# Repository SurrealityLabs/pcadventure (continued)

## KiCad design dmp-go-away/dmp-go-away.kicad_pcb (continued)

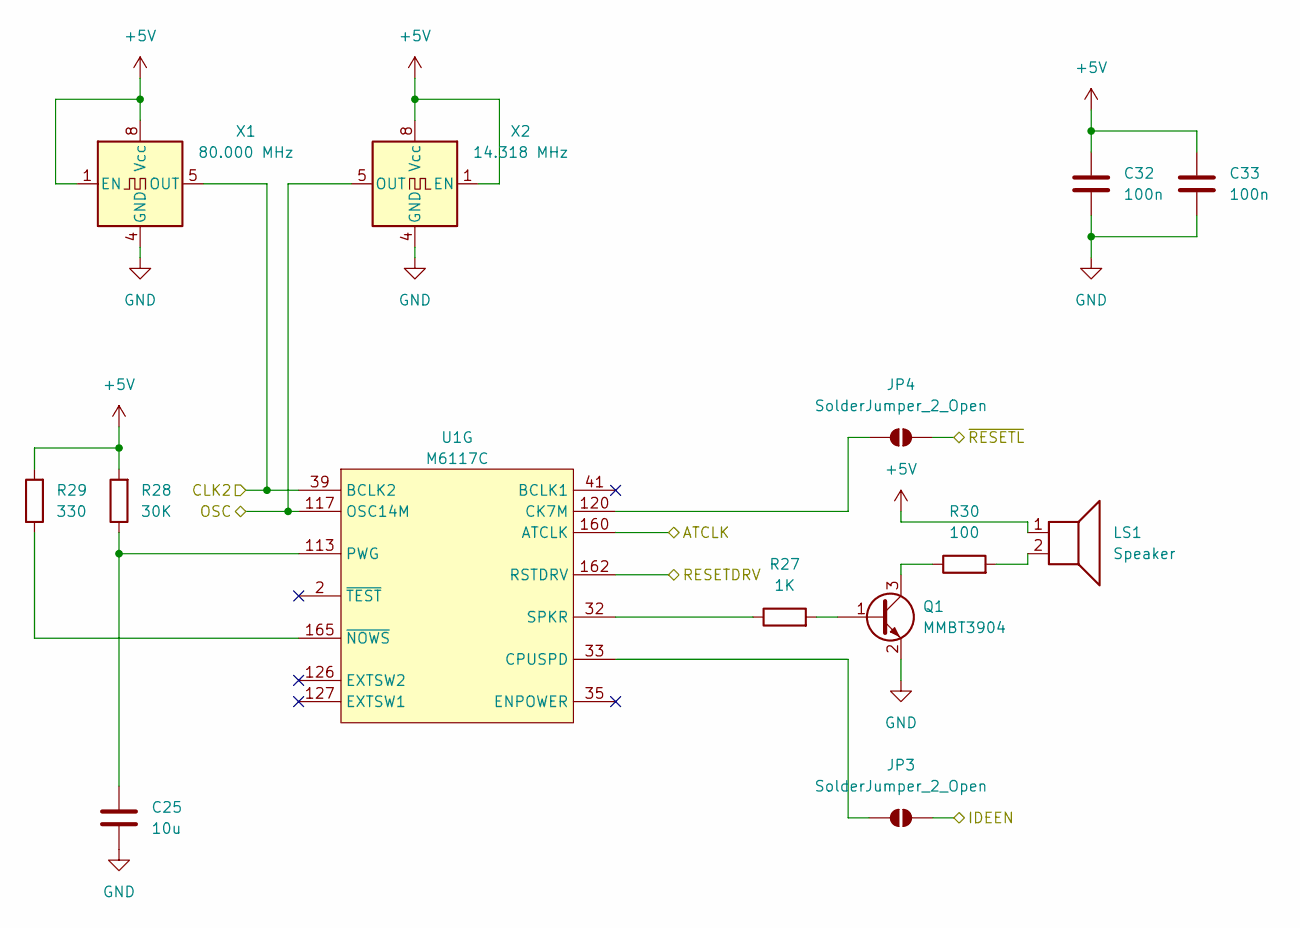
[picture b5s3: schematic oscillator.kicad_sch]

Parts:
C25: 10u; C_1206_3216Metric_Pad1.33x1.80mm_HandSolder
C32, C33: 100n; C_0603_1608Metric_Pad1.08x0.95mm_HandSolder
JP3, JP4: SolderJumper_2_Open; SolderJumper-2_P1.3mm_Open_RoundedPad1.0x1.5mm
LS1: Speaker; Buzzer_TDK_PS1240P02BT_D12.2mm_H6.5mm
Q1: MMBT3904; SOT-23
R27: 1K; R_0603_1608Metric_Pad0.98x0.95mm_HandSolder
R28: 30K; R_0603_1608Metric_Pad0.98x0.95mm_HandSolder
R29: 330; R_0603_1608Metric_Pad0.98x0.95mm_HandSolder
R30: 100; R_0603_1608Metric_Pad0.98x0.95mm_HandSolder
U1: M6117C; PQFP-208_28x28mm_P0.5mm
X1: 80.000 MHz; Oscillator_DIP-8; Digikey XC283-ND
X2: 14.318 MHz; Oscillator_DIP-8; Digikey 110-MXO45HS-3C-14M318180-ND

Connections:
+5V: C32.1, C33.1, LS1.1, R28.2, R29.2, X1.1 (EN), X1.8 (Vcc), X2.1 (EN), X2.8 (Vcc); also elsewhere on the board
/ATCLK: U1.160 (ATCLK); also elsewhere on the board
/IDEEN: JP3.2 (B); also elsewhere on the board
/OSC: U1.117 (OSC14M), X2.5 (OUT); also elsewhere on the board
/Oscillator/CLK2: U1.39 (BCLK2), X1.5 (OUT)
/RESETDRV: U1.162 (RSTDRV); also elsewhere on the board
/~RESETL: JP4.2 (B); also elsewhere on the board
GND: C25.2, C32.2, C33.2, Q1.2 (E), X1.4 (GND), X2.4 (GND); also elsewhere on the board
unnamed: JP3.1 (A), U1.33 (CPUSPD)
unnamed: JP4.1 (A), U1.120 (CK7M)
unnamed: LS1.2, R30.2
unnamed: Q1.1 (B), R27.2
unnamed: Q1.3 (C), R30.1
unnamed: C25.1, R28.1, U1.113 (PWG)
unnamed: R27.1, U1.32 (SPKR)
unnamed: R29.1, U1.165 (~NOWS)

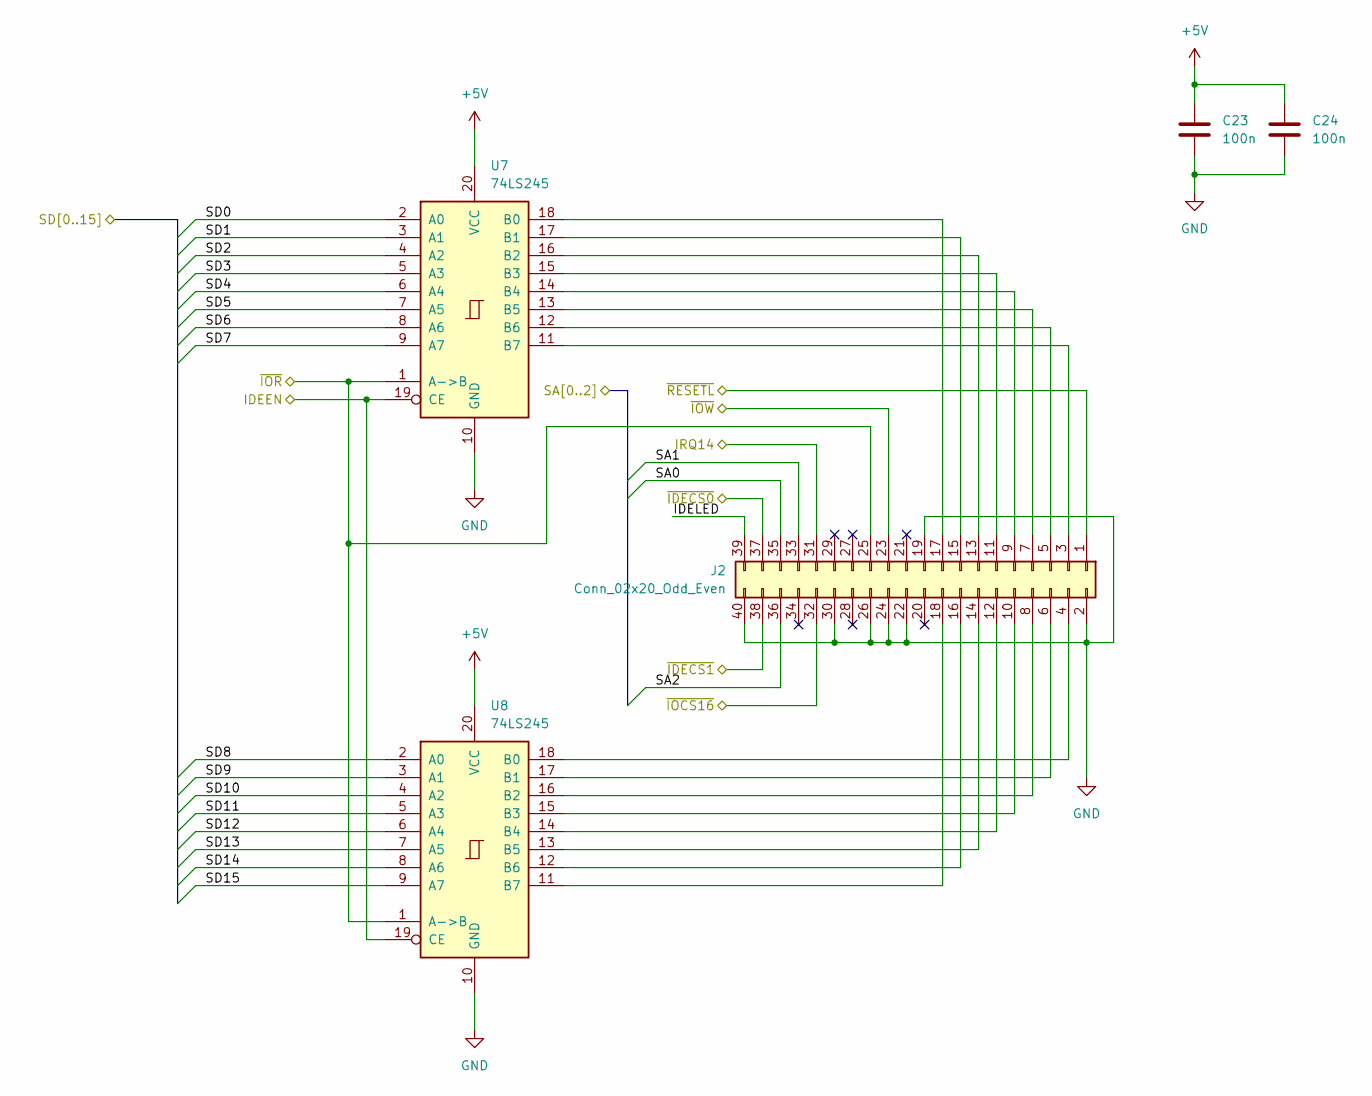
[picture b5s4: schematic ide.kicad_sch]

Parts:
C23, C24: 100n; C_0603_1608Metric_Pad1.08x0.95mm_HandSolder
J2: Conn_02x20_Odd_Even; IDC-Header_2x20_P2.54mm_Vertical
U7, U8: 74LS245; SOIC-20W_7.5x12.8mm_P1.27mm

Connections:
+5V: C23.1, C24.1, U7.20 (VCC), U8.20 (VCC); also elsewhere on the board
/IDE/IDELED: J2.39
/IDEEN: U7.19 (CE), U8.19 (CE); also elsewhere on the board
/IRQ14: J2.31; also elsewhere on the board
/SA0: J2.35; also elsewhere on the board
/SA1: J2.33; also elsewhere on the board
/SA2: J2.36; also elsewhere on the board
/SD0: U7.2 (A0); also elsewhere on the board
/SD1: U7.3 (A1); also elsewhere on the board
/SD2: U7.4 (A2); also elsewhere on the board
/SD3: U7.5 (A3); also elsewhere on the board
/SD4: U7.6 (A4); also elsewhere on the board
/SD5: U7.7 (A5); also elsewhere on the board
/SD6: U7.8 (A6); also elsewhere on the board
/SD7: U7.9 (A7); also elsewhere on the board
/SD8: U8.2 (A0); also elsewhere on the board
/SD9: U8.3 (A1); also elsewhere on the board
/SD10: U8.4 (A2); also elsewhere on the board
/SD11: U8.5 (A3); also elsewhere on the board
/SD12: U8.6 (A4); also elsewhere on the board
/SD13: U8.7 (A5); also elsewhere on the board
/SD14: U8.8 (A6); also elsewhere on the board
/SD15: U8.9 (A7); also elsewhere on the board
/~IDECS0: J2.37; also elsewhere on the board
/~IDECS1: J2.38; also elsewhere on the board
/~IO16: J2.32; also elsewhere on the board
/~IOR: J2.25, U7.1 (A->B), U8.1 (A->B); also elsewhere on the board
/~IOW: J2.23; also elsewhere on the board
/~RESETL: J2.1; also elsewhere on the board
GND: C23.2, C24.2, J2.2, J2.19, J2.22, J2.24, J2.26, J2.30, J2.40, U7.10 (GND), U8.10 (GND); also elsewhere on the board
unnamed: J2.3, U7.11 (B7)
unnamed: J2.4, U8.18 (B0)
unnamed: J2.5, U7.12 (B6)
unnamed: J2.6, U8.17 (B1)
unnamed: J2.7, U7.13 (B5)
unnamed: J2.8, U8.16 (B2)
unnamed: J2.9, U7.14 (B4)
unnamed: J2.10, U8.15 (B3)
unnamed: J2.11, U7.15 (B3)
unnamed: J2.12, U8.14 (B4)
unnamed: J2.13, U7.16 (B2)
unnamed: J2.14, U8.13 (B5)
unnamed: J2.15, U7.17 (B1)
unnamed: J2.16, U8.12 (B6)
unnamed: J2.17, U7.18 (B0)
unnamed: J2.18, U8.11 (B7)

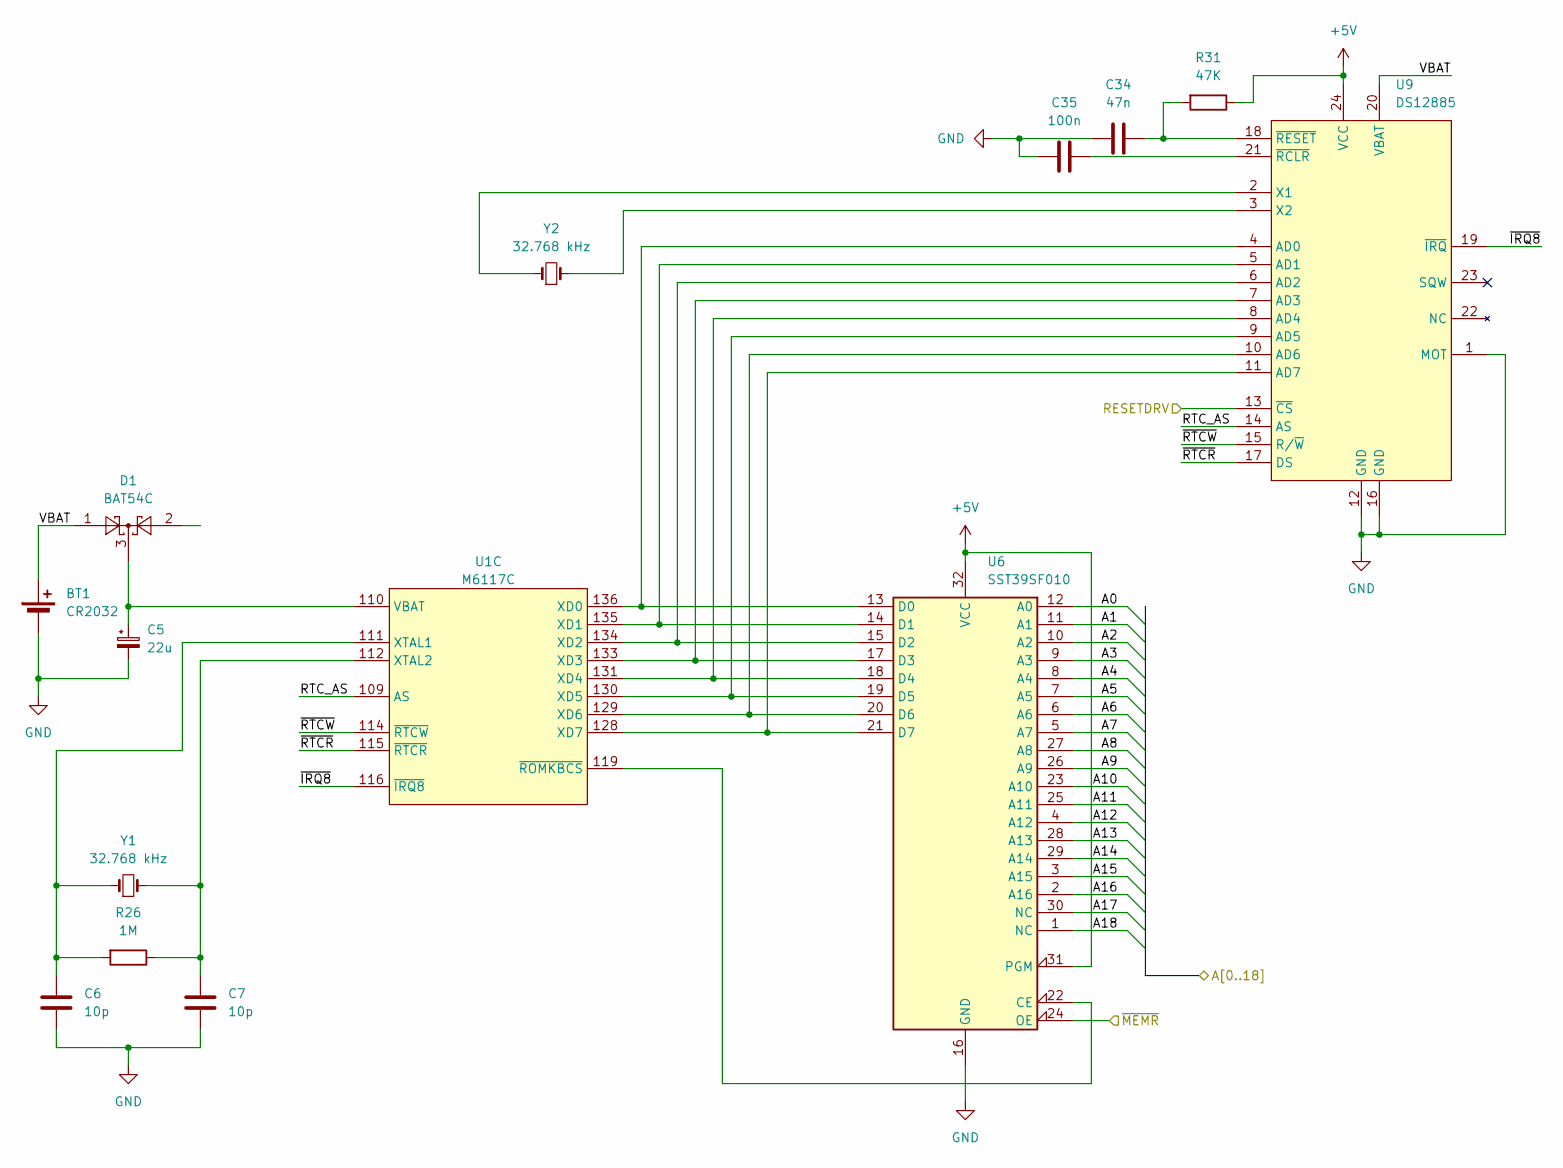
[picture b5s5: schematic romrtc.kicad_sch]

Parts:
BT1: CR2032; BatteryHolder_Keystone_1060_1x2032
C5: 22u; CP_Elec_5x5.3
C6, C7: 10p; C_0603_1608Metric_Pad1.08x0.95mm_HandSolder
C34: 47n; C_0603_1608Metric_Pad1.08x0.95mm_HandSolder
C35: 100n; C_0603_1608Metric_Pad1.08x0.95mm_HandSolder
D1: BAT54C; SOT-23
R26: 1M; R_0603_1608Metric_Pad0.98x0.95mm_HandSolder
R31: 47K; R_0603_1608Metric_Pad0.98x0.95mm_HandSolder
U1: M6117C; PQFP-208_28x28mm_P0.5mm
U6: SST39SF010; DIP-32_W15.24mm_Socket
U9: DS12885; DIP-24_W15.24mm
Y1, Y2: 32.768 kHz; Crystal_AT310_D3.0mm_L10.0mm_Vertical

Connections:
+5V: R31.1, U6.31 (PGM), U6.32 (VCC), U9.24 (VCC); also elsewhere on the board
/RESETDRV: U9.13 (~CS); also elsewhere on the board
/ROM RTC/RTC_AS: U1.109 (AS), U9.14 (AS)
/ROM RTC/VBAT: BT1.1 (+), D1.1, U9.20 (VBAT)
/ROM RTC/~IRQ8: U1.116 (~IRQ8), U9.19 (~IRQ)
/ROM RTC/~RTCR: U1.115 (~RTCR), U9.17 (DS)
/ROM RTC/~RTCW: U1.114 (~RTCW), U9.15 (R/~W)
/SA0: U6.12 (A0); also elsewhere on the board
/SA1: U6.11 (A1); also elsewhere on the board
/SA2: U6.10 (A2); also elsewhere on the board
/SA3: U6.9 (A3); also elsewhere on the board
/SA4: U6.8 (A4); also elsewhere on the board
/SA5: U6.7 (A5); also elsewhere on the board
/SA6: U6.6 (A6); also elsewhere on the board
/SA7: U6.5 (A7); also elsewhere on the board
/SA8: U6.27 (A8); also elsewhere on the board
/SA9: U6.26 (A9); also elsewhere on the board
/SA10: U6.23 (A10); also elsewhere on the board
/SA11: U6.25 (A11); also elsewhere on the board
/SA12: U6.4 (A12); also elsewhere on the board
/SA13: U6.28 (A13); also elsewhere on the board
/SA14: U6.29 (A14); also elsewhere on the board
/SA15: U6.3 (A15); also elsewhere on the board
/SA16: U6.2 (A16); also elsewhere on the board
/SA17: U6.30 (NC); also elsewhere on the board
/SA18: U6.1 (NC); also elsewhere on the board
/~MEMR: U6.24 (OE)
GND: BT1.2 (-), C5.2, C6.2, C7.2, C34.2, C35.2, U6.16 (GND), U9.1 (MOT), U9.12 (GND), U9.16 (GND); also elsewhere on the board
unnamed: C5.1, D1.3, U1.110 (VBAT)
unnamed: U1.136 (XD0), U6.13 (D0), U9.4 (AD0)
unnamed: U1.135 (XD1), U6.14 (D1), U9.5 (AD1)
unnamed: U1.134 (XD2), U6.15 (D2), U9.6 (AD2)
unnamed: U1.133 (XD3), U6.17 (D3), U9.7 (AD3)
unnamed: U1.131 (XD4), U6.18 (D4), U9.8 (AD4)
unnamed: U1.130 (XD5), U6.19 (D5), U9.9 (AD5)
unnamed: U1.129 (XD6), U6.20 (D6), U9.10 (AD6)
unnamed: U1.128 (XD7), U6.21 (D7), U9.11 (AD7)
unnamed: C6.1, R26.2, U1.111 (XTAL1), Y1.1
unnamed: C7.1, R26.1, U1.112 (XTAL2), Y1.2
unnamed: U1.119 (~ROMKBCS), U6.22 (CE)
unnamed: U9.2 (X1), Y2.1
unnamed: U9.3 (X2), Y2.2
unnamed: C35.1, U9.21 (~RCLR)
unnamed: C34.1, R31.2, U9.18 (~RESET)

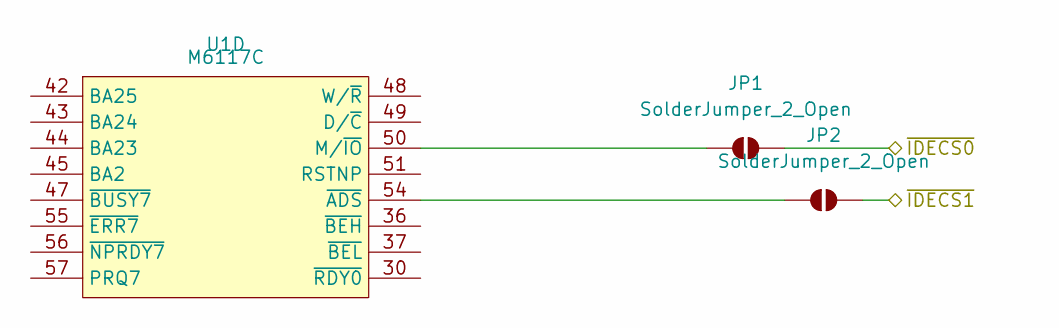
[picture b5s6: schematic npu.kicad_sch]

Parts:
JP1, JP2: SolderJumper_2_Open; SolderJumper-2_P1.3mm_Open_RoundedPad1.0x1.5mm
U1: M6117C; PQFP-208_28x28mm_P0.5mm

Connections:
/~IDECS0: JP1.2 (B); also elsewhere on the board
/~IDECS1: JP2.2 (B); also elsewhere on the board
unnamed: JP1.1 (A), U1.50 (M/~IO)
unnamed: JP2.1 (A), U1.54 (~ADS)

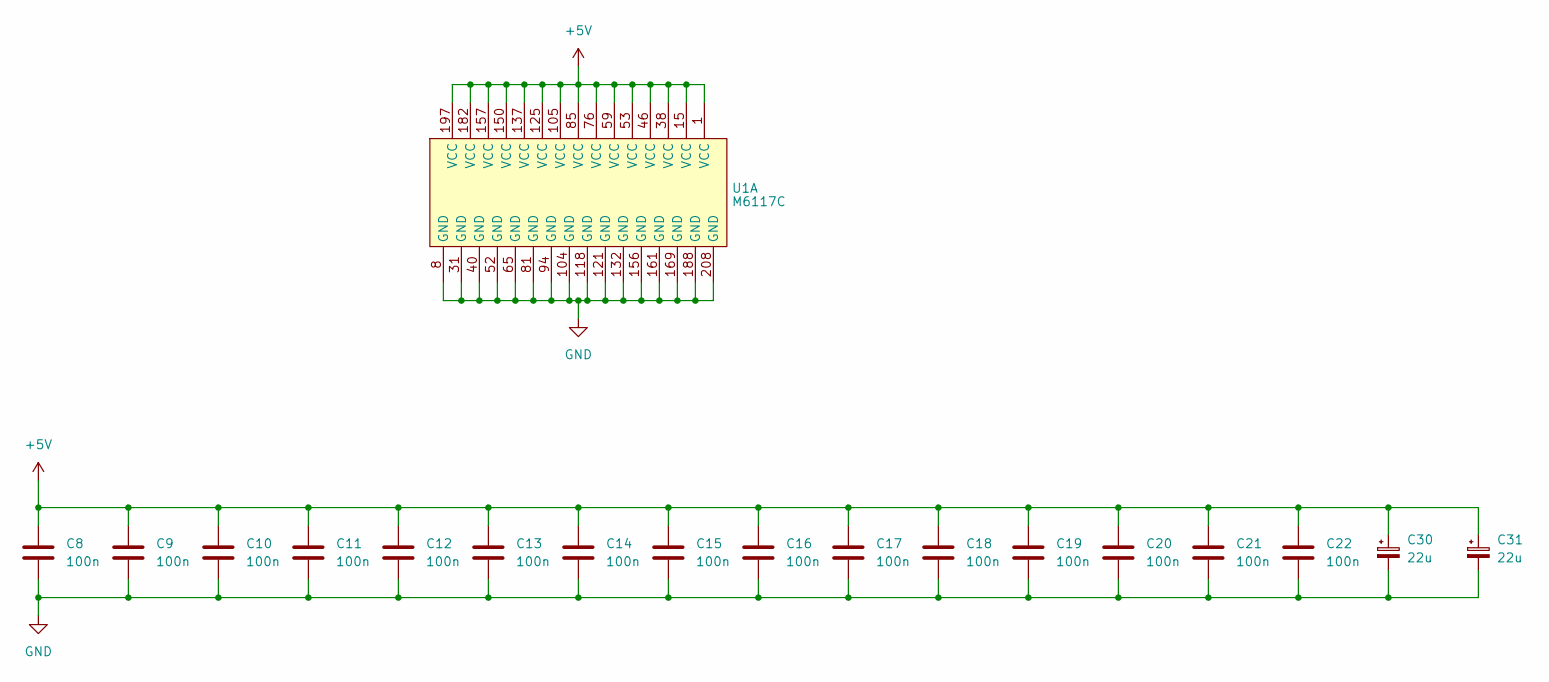
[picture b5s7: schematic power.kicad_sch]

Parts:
C8, C9, C10, C11, C12, C13, C14, C15, C16, C17, C18, C19, C20, C21, C22: 100n; C_0603_1608Metric_Pad1.08x0.95mm_HandSolder
C30, C31: 22u; CP_Elec_5x5.3
U1: M6117C; PQFP-208_28x28mm_P0.5mm

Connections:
+5V: C8.1, C9.1, C10.1, C11.1, C12.1, C13.1, C14.1, C15.1, C16.1, C17.1, C18.1, C19.1, C20.1, C21.1, C22.1, C30.1, C31.1, U1.1 (VCC), U1.15 (VCC), U1.38 (VCC), U1.46 (VCC), U1.53 (VCC), U1.59 (VCC), U1.76 (VCC), U1.85 (VCC), U1.105 (VCC), U1.125 (VCC), U1.137 (VCC), U1.150 (VCC), U1.157 (VCC), U1.182 (VCC), U1.197 (VCC); also elsewhere on the board
GND: C8.2, C9.2, C10.2, C11.2, C12.2, C13.2, C14.2, C15.2, C16.2, C17.2, C18.2, C19.2, C20.2, C21.2, C22.2, C30.2, C31.2, U1.8 (GND), U1.31 (GND), U1.40 (GND), U1.52 (GND), U1.65 (GND), U1.81 (GND), U1.94 (GND), U1.104 (GND), U1.118 (GND), U1.121 (GND), U1.132 (GND), U1.156 (GND), U1.161 (GND), U1.169 (GND), U1.188 (GND), U1.208 (GND); also elsewhere on the board

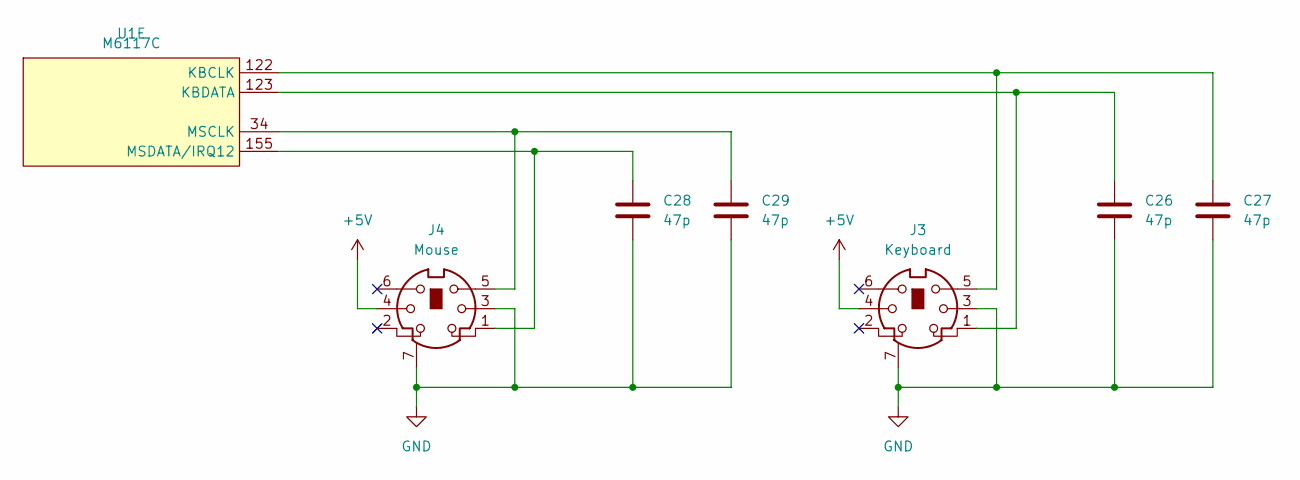
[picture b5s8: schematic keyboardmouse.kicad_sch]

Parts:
C26, C27, C28, C29: 47p; C_0603_1608Metric_Pad1.08x0.95mm_HandSolder
J3: Keyboard; CUI_MD-60SGK
J4: Mouse; CUI_MD-60SGK
U1: M6117C; PQFP-208_28x28mm_P0.5mm

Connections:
+5V: J3.4, J4.4; also elsewhere on the board
GND: C26.2, C27.2, C28.2, C29.2, J3.3, J3.7, J4.3, J4.7; also elsewhere on the board
unnamed: C27.1, J3.5, U1.122 (KBCLK)
unnamed: C26.1, J3.1, U1.123 (KBDATA)
unnamed: C29.1, J4.5, U1.34 (MSCLK)
unnamed: C28.1, J4.1, U1.155 (MSDATA/IRQ12)

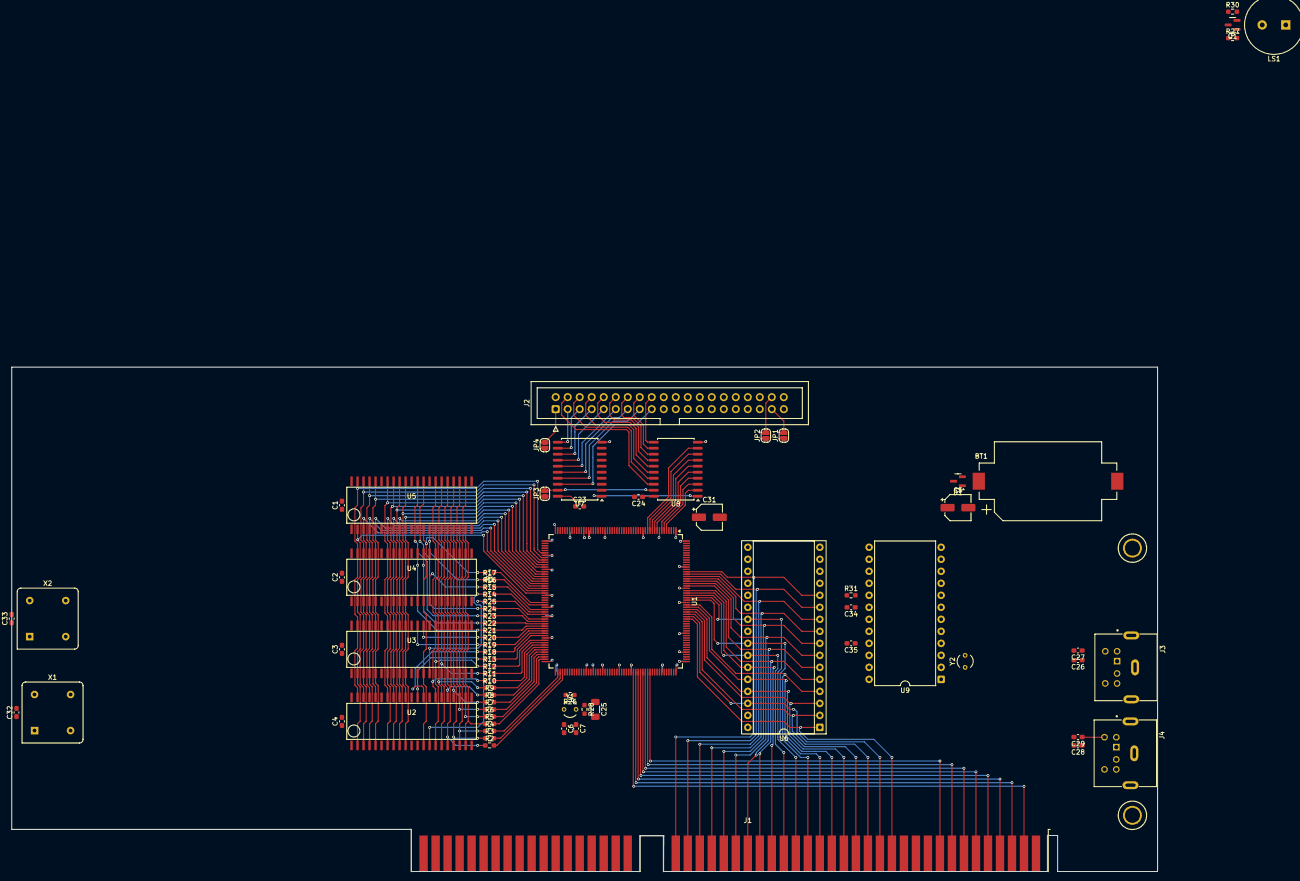
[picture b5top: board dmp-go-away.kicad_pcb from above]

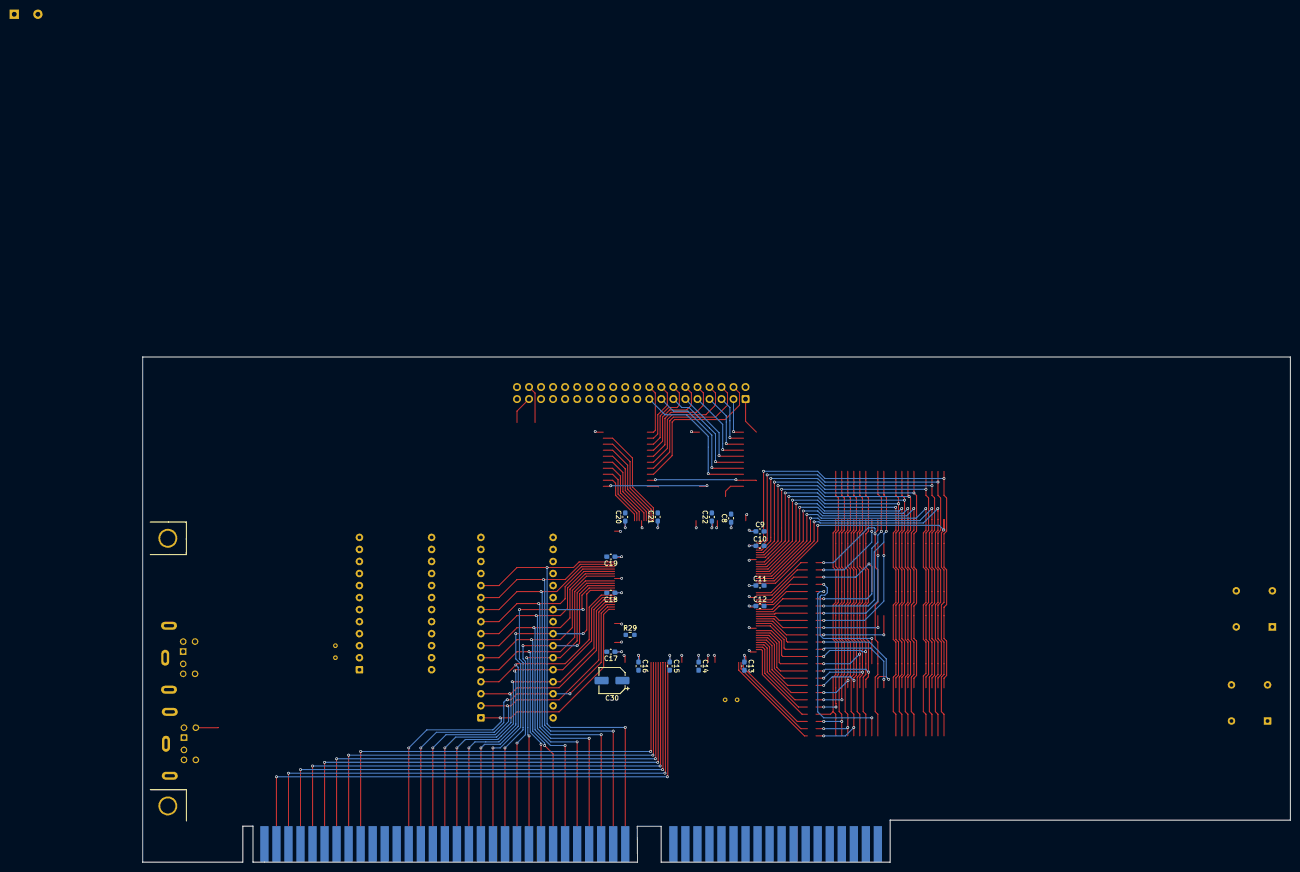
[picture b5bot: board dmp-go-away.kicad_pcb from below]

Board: 2 copper layers, 242.4 x 106.7 mm, 92 parts (17 on the bottom side), 210 nets.

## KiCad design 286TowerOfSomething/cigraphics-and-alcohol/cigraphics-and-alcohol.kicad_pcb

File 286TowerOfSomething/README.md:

THE PLAN:
- I have a 14-slot ISA backplane from Surplus Gizmos. That will form the basis of the system. Because there are so many slots on the backplane, the individual cards can be single-function (allowing a smaller and therefore cheaper PCB)
- CPU, ROM, RAM, Chipset, and keyboard controller will go on an ISA card.
- Video card will be a TVGA8900D card that I already ordered.
- I will make a dual 16C550-based serial card, with an option to convert one serial port to a PS/2 mouse input through an ATMEGA328P running some open-source firmware. That covers serial port and mouse input.
- I will make a 16-bit IDE card (using a PAL and some bus transceivers) that has an Option ROM containing the XTIDE BIOS. That'll provide fixed storage (through CF card, optical drive, or SD to IDE adapter)
- I will make a parallel card using an EPP/ECP parallel port controller, so that we can add things like ZIP drives or scanners or what not if we find them.
- I will make a floppy controller using a floppy controller to be named later
- For sound card, probably a PicoGUS or whatever Cirrus Logic chip I have available
- Something simple for Ethernet, like an RTL8019. Might be cheaper to build one than buy one at this point - the chip is $5, and cards are going for like $40+. Pretty sure those were $10-$20 when new.
- For convenience, a CH375-based USB mass storage card.

FUTURE PLANS:
- Can make an upgraded CPU card with an M6117D chip from DM&P/nVidia. 386SX 40 MHz system on a chip, might still be made in 2024.
- Can make an upgraded CPU card with a 486 chip and chipset, if we can find one. Add VLB video onto that card for faaaaaast gaming - has to be on the card, though, because the backplane won't do VLB.

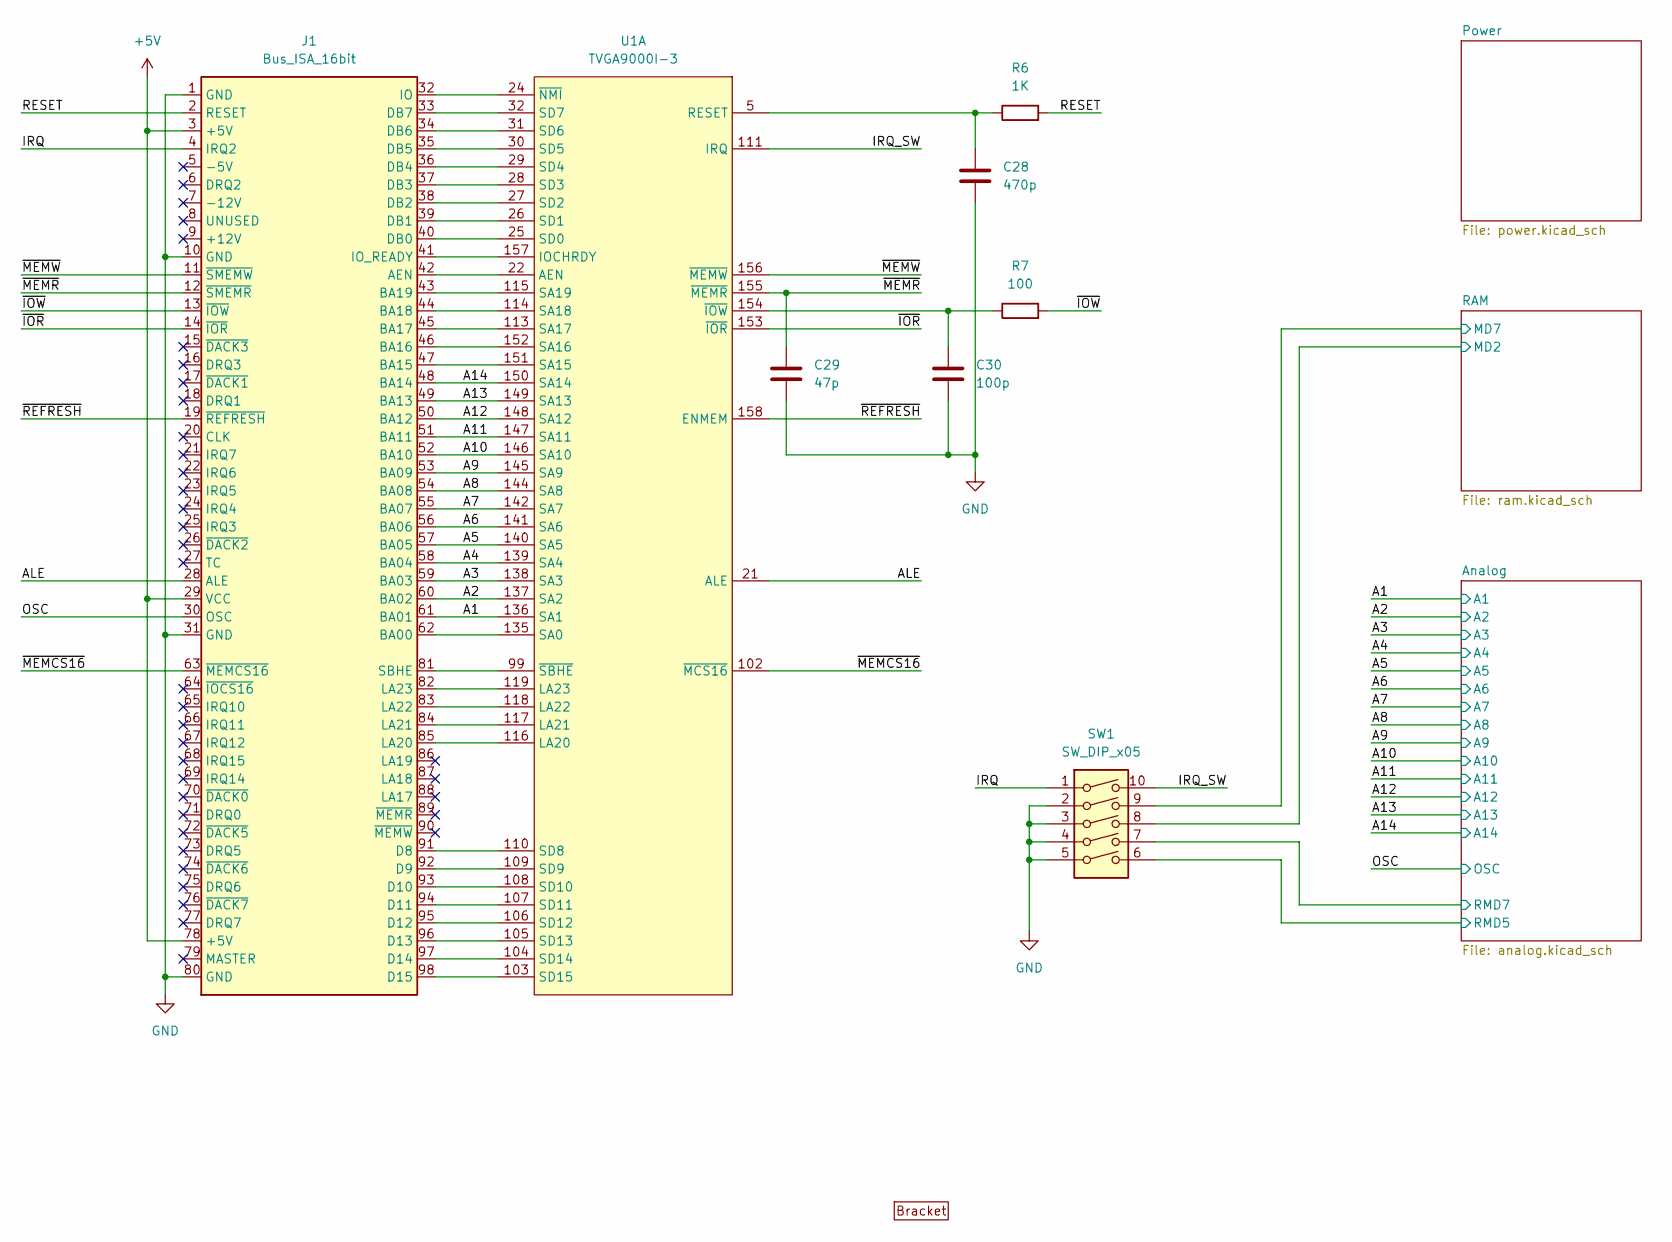
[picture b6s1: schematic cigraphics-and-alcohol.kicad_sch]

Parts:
C28: 470p; C_0603_1608Metric_Pad1.08x0.95mm_HandSolder
C29: 47p; C_0603_1608Metric_Pad1.08x0.95mm_HandSolder
C30: 100p; C_0603_1608Metric_Pad1.08x0.95mm_HandSolder
J1: Bus_ISA_16bit; BUS_AT
R6: 1K; R_0603_1608Metric_Pad0.98x0.95mm_HandSolder
R7: 100; R_0603_1608Metric_Pad0.98x0.95mm_HandSolder
SW1: SW_DIP_x05; SW_DIP_SPSTx05_Slide_9.78x14.88mm_W7.62mm_P2.54mm
U1: TVGA9000I-3; PQFP-160_28x28mm_P0.65mm
U7: PC_BRACKET_ISA_KEYSTONE_9200_Rev1_1

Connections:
+5V: J1.3 (+5V), J1.29 (VCC), J1.78 (+5V); also elsewhere on the board
/A1: J1.61 (BA01), U1.136 (SA1); also elsewhere on the board
/A2: J1.60 (BA02), U1.137 (SA2); also elsewhere on the board
/A3: J1.59 (BA03), U1.138 (SA3); also elsewhere on the board
/A4: J1.58 (BA04), U1.139 (SA4); also elsewhere on the board
/A5: J1.57 (BA05), U1.140 (SA5); also elsewhere on the board
/A6: J1.56 (BA06), U1.141 (SA6); also elsewhere on the board
/A7: J1.55 (BA07), U1.142 (SA7); also elsewhere on the board
/A8: J1.54 (BA08), U1.144 (SA8); also elsewhere on the board
/A9: J1.53 (BA09), U1.145 (SA9); also elsewhere on the board
/A10: J1.52 (BA10), U1.146 (SA10); also elsewhere on the board
/A11: J1.51 (BA11), U1.147 (SA11); also elsewhere on the board
/A12: J1.50 (BA12), U1.148 (SA12); also elsewhere on the board
/A13: J1.49 (BA13), U1.149 (SA13); also elsewhere on the board
/A14: J1.48 (BA14), U1.150 (SA14); also elsewhere on the board
/ALE: J1.28 (ALE), U1.21 (ALE)
/Analog/RMD5: SW1.6; also elsewhere on the board
/Analog/RMD7: SW1.7; also elsewhere on the board
/IRQ: J1.4 (IRQ2), SW1.1
/IRQ_SW: SW1.10, U1.111 (IRQ)
/OSC: J1.30 (OSC); also elsewhere on the board
/RAM/MD2: SW1.8; also elsewhere on the board
/RAM/MD7: SW1.9; also elsewhere on the board
/RESET: J1.2 (RESET), R6.2
/~IOR: J1.14 (~IOR), U1.153 (~IOR)
/~IOW: J1.13 (~IOW), R7.2
/~MEMCS16: J1.63 (~MEMCS16), U1.102 (~MCS16)
/~MEMR: C29.1, J1.12 (~SMEMR), U1.155 (~MEMR)
/~MEMW: J1.11 (~SMEMW), U1.156 (~MEMW)
/~REFRESH: J1.19 (~REFRESH), U1.158 (ENMEM)
GND: C28.2, C29.2, C30.2, J1.1 (GND), J1.10 (GND), J1.31 (GND), J1.80 (GND), SW1.2, SW1.3, SW1.4, SW1.5; also elsewhere on the board
unnamed: J1.42 (AEN), U1.22 (AEN)
unnamed: J1.62 (BA00), U1.135 (SA0)
unnamed: J1.47 (BA15), U1.151 (SA15)
unnamed: J1.46 (BA16), U1.152 (SA16)
unnamed: J1.45 (BA17), U1.113 (SA17)
unnamed: J1.44 (BA18), U1.114 (SA18)
unnamed: J1.43 (BA19), U1.115 (SA19)
unnamed: J1.91 (D8), U1.110 (SD8)
unnamed: J1.92 (D9), U1.109 (SD9)
unnamed: J1.93 (D10), U1.108 (SD10)
unnamed: J1.94 (D11), U1.107 (SD11)
unnamed: J1.95 (D12), U1.106 (SD12)
unnamed: J1.96 (D13), U1.105 (SD13)
unnamed: J1.97 (D14), U1.104 (SD14)
unnamed: J1.98 (D15), U1.103 (SD15)
unnamed: J1.40 (DB0), U1.25 (SD0)
unnamed: J1.39 (DB1), U1.26 (SD1)
unnamed: J1.38 (DB2), U1.27 (SD2)
unnamed: J1.37 (DB3), U1.28 (SD3)
unnamed: J1.36 (DB4), U1.29 (SD4)
unnamed: J1.35 (DB5), U1.30 (SD5)
unnamed: J1.34 (DB6), U1.31 (SD6)
unnamed: J1.33 (DB7), U1.32 (SD7)
unnamed: J1.32 (IO), U1.24 (~NMI)
unnamed: J1.41 (IO_READY), U1.157 (IOCHRDY)
unnamed: J1.85 (LA20), U1.116 (LA20)
unnamed: J1.84 (LA21), U1.117 (LA21)
unnamed: J1.83 (LA22), U1.118 (LA22)
unnamed: J1.82 (LA23), U1.119 (LA23)
unnamed: J1.81 (SBHE), U1.99 (~SBHE)
unnamed: C28.1, R6.1, U1.5 (RESET)
unnamed: C30.1, R7.1, U1.154 (~IOW)

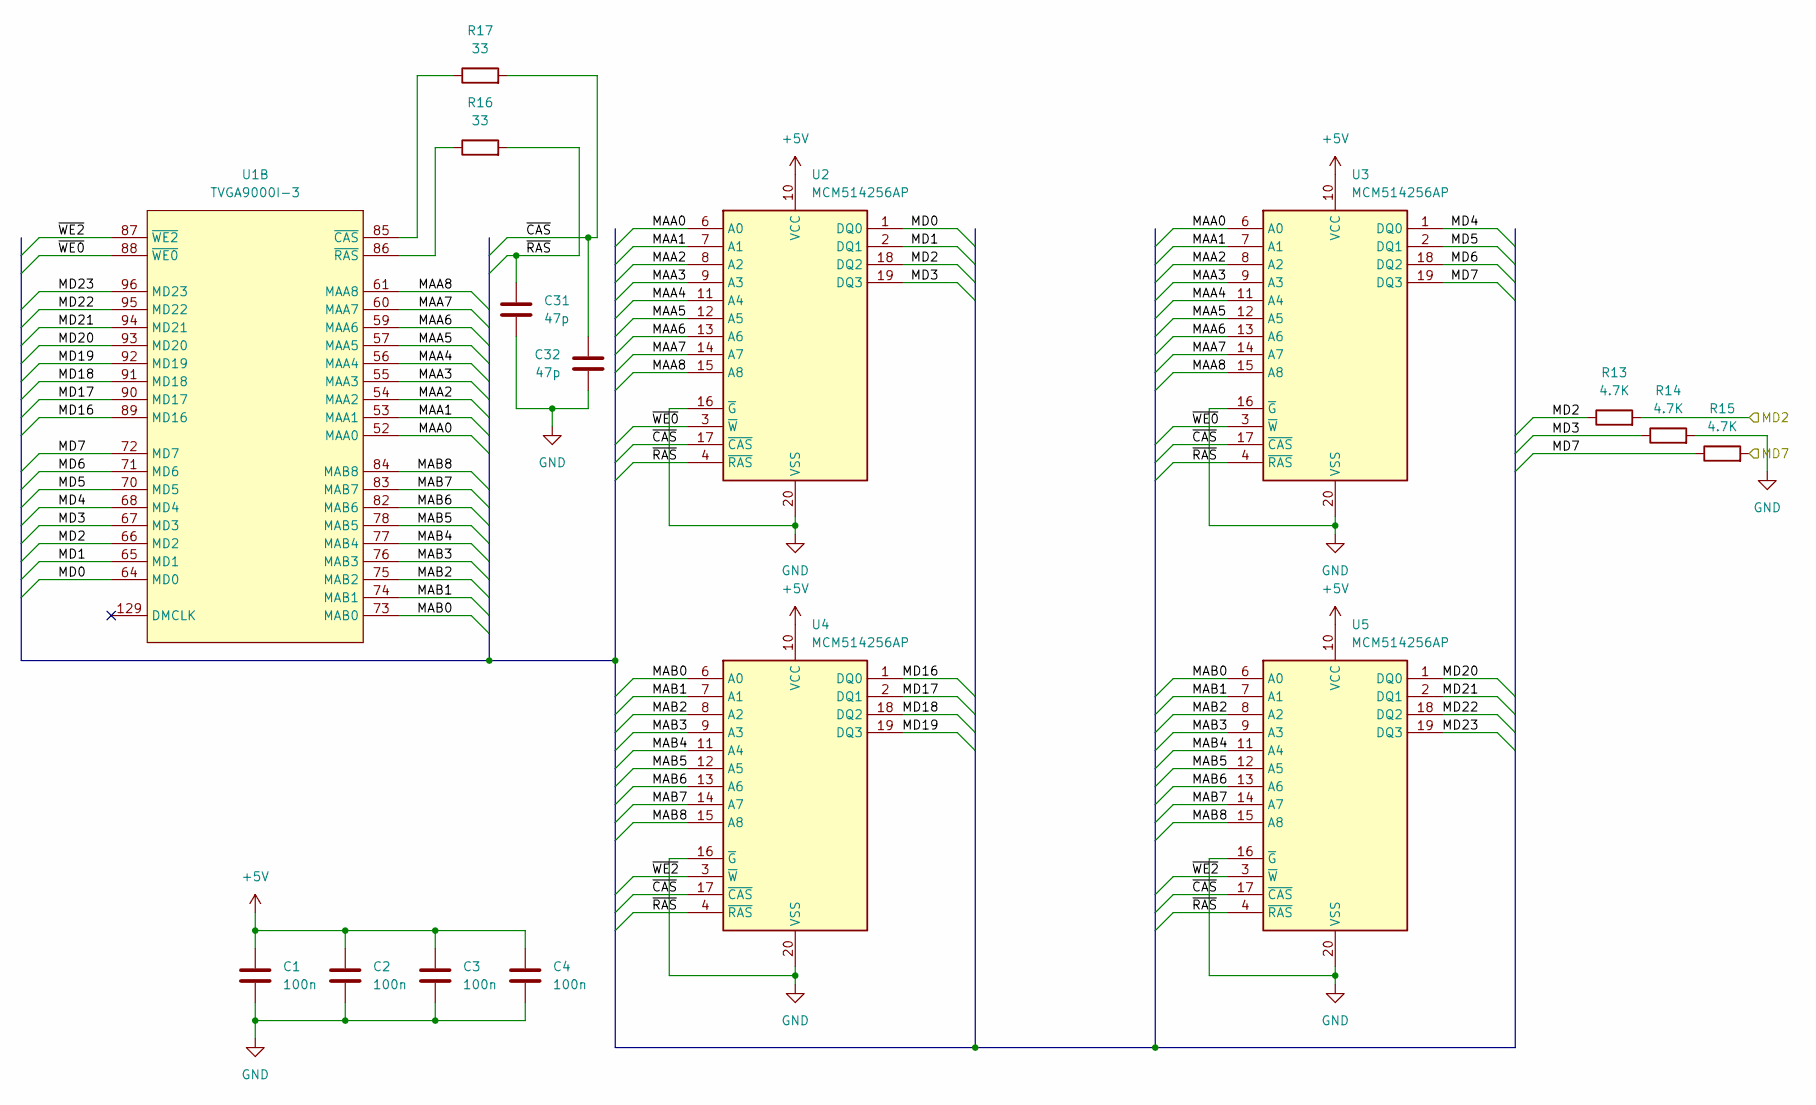
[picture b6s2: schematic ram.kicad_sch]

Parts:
C1, C2, C3, C4: 100n; C_0603_1608Metric_Pad1.08x0.95mm_HandSolder
C31, C32: 47p; C_0603_1608Metric_Pad1.08x0.95mm_HandSolder
R13, R14, R15: 4.7K; R_0603_1608Metric_Pad0.98x0.95mm_HandSolder
R16, R17: 33; R_0603_1608Metric_Pad0.98x0.95mm_HandSolder
U1: TVGA9000I-3; PQFP-160_28x28mm_P0.65mm
U2, U3, U4, U5: MCM514256AP; DIP-20_W7.62mm

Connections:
+5V: C1.1, C2.1, C3.1, C4.1, U2.10 (VCC), U3.10 (VCC), U4.10 (VCC), U5.10 (VCC); also elsewhere on the board
/RAM/MAA0: U1.52 (MAA0), U2.6 (A0), U3.6 (A0)
/RAM/MAA1: U1.53 (MAA1), U2.7 (A1), U3.7 (A1)
/RAM/MAA2: U1.54 (MAA2), U2.8 (A2), U3.8 (A2)
/RAM/MAA3: U1.55 (MAA3), U2.9 (A3), U3.9 (A3)
/RAM/MAA4: U1.56 (MAA4), U2.11 (A4), U3.11 (A4)
/RAM/MAA5: U1.57 (MAA5), U2.12 (A5), U3.12 (A5)
/RAM/MAA6: U1.59 (MAA6), U2.13 (A6), U3.13 (A6)
/RAM/MAA7: U1.60 (MAA7), U2.14 (A7), U3.14 (A7)
/RAM/MAA8: U1.61 (MAA8), U2.15 (A8), U3.15 (A8)
/RAM/MAB0: U1.73 (MAB0), U4.6 (A0), U5.6 (A0)
/RAM/MAB1: U1.74 (MAB1), U4.7 (A1), U5.7 (A1)
/RAM/MAB2: U1.75 (MAB2), U4.8 (A2), U5.8 (A2)
/RAM/MAB3: U1.76 (MAB3), U4.9 (A3), U5.9 (A3)
/RAM/MAB4: U1.77 (MAB4), U4.11 (A4), U5.11 (A4)
/RAM/MAB5: U1.78 (MAB5), U4.12 (A5), U5.12 (A5)
/RAM/MAB6: U1.82 (MAB6), U4.13 (A6), U5.13 (A6)
/RAM/MAB7: U1.83 (MAB7), U4.14 (A7), U5.14 (A7)
/RAM/MAB8: U1.84 (MAB8), U4.15 (A8), U5.15 (A8)
/RAM/MD0: U1.64 (MD0), U2.1 (DQ0)
/RAM/MD1: U1.65 (MD1), U2.2 (DQ1)
/RAM/MD2: R13.1, R13.2, U1.66 (MD2), U2.18 (DQ2); also elsewhere on the board
/RAM/MD3: R14.1, U1.67 (MD3), U2.19 (DQ3)
/RAM/MD4: U1.68 (MD4), U3.1 (DQ0)
/RAM/MD5: U1.70 (MD5), U3.2 (DQ1)
/RAM/MD6: U1.71 (MD6), U3.18 (DQ2)
/RAM/MD7: R15.1, R15.2, U1.72 (MD7), U3.19 (DQ3); also elsewhere on the board
/RAM/MD16: U1.89 (MD16), U4.1 (DQ0)
/RAM/MD17: U1.90 (MD17), U4.2 (DQ1)
/RAM/MD18: U1.91 (MD18), U4.18 (DQ2)
/RAM/MD19: U1.92 (MD19), U4.19 (DQ3)
/RAM/MD20: U1.93 (MD20), U5.1 (DQ0)
/RAM/MD21: U1.94 (MD21), U5.2 (DQ1)
/RAM/MD22: U1.95 (MD22), U5.18 (DQ2)
/RAM/MD23: U1.96 (MD23), U5.19 (DQ3)
/RAM/~CAS: C32.1, R17.2, U2.17 (~CAS), U3.17 (~CAS), U4.17 (~CAS), U5.17 (~CAS)
/RAM/~RAS: C31.1, R16.2, U2.4 (~RAS), U3.4 (~RAS), U4.4 (~RAS), U5.4 (~RAS)
/RAM/~WE0: U1.88 (~WE0), U2.3 (~W), U3.3 (~W)
/RAM/~WE2: U1.87 (~WE2), U4.3 (~W), U5.3 (~W)
GND: C1.2, C2.2, C3.2, C4.2, C31.2, C32.2, R14.2, U2.16 (~G), U2.20 (VSS), U3.16 (~G), U3.20 (VSS), U4.16 (~G), U4.20 (VSS), U5.16 (~G), U5.20 (VSS); also elsewhere on the board
unnamed: R17.1, U1.85 (~CAS)
unnamed: R16.1, U1.86 (~RAS)
